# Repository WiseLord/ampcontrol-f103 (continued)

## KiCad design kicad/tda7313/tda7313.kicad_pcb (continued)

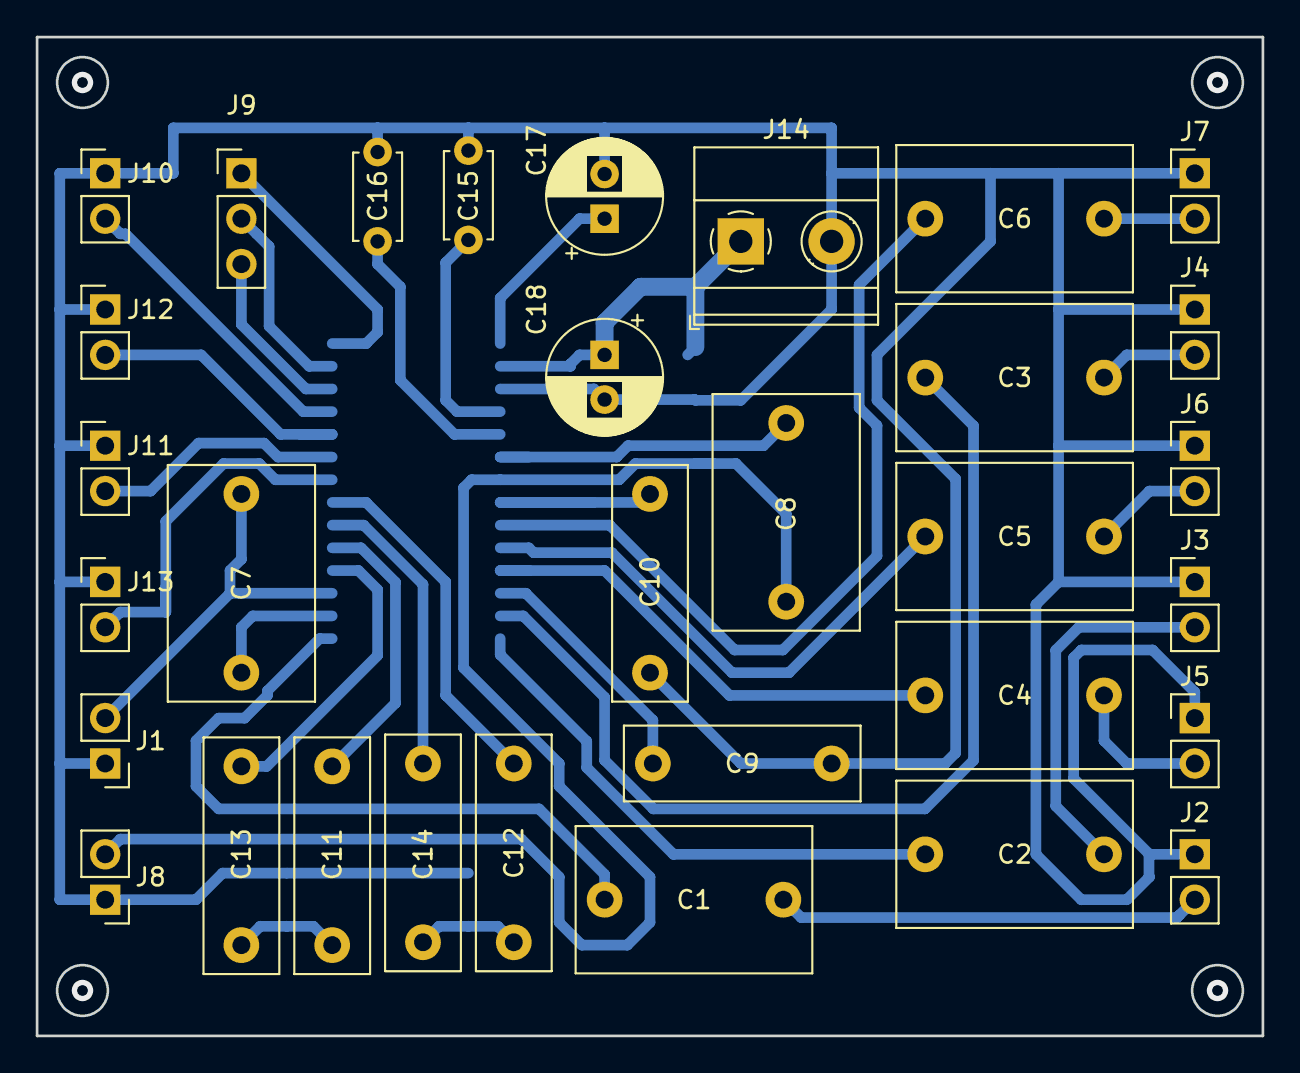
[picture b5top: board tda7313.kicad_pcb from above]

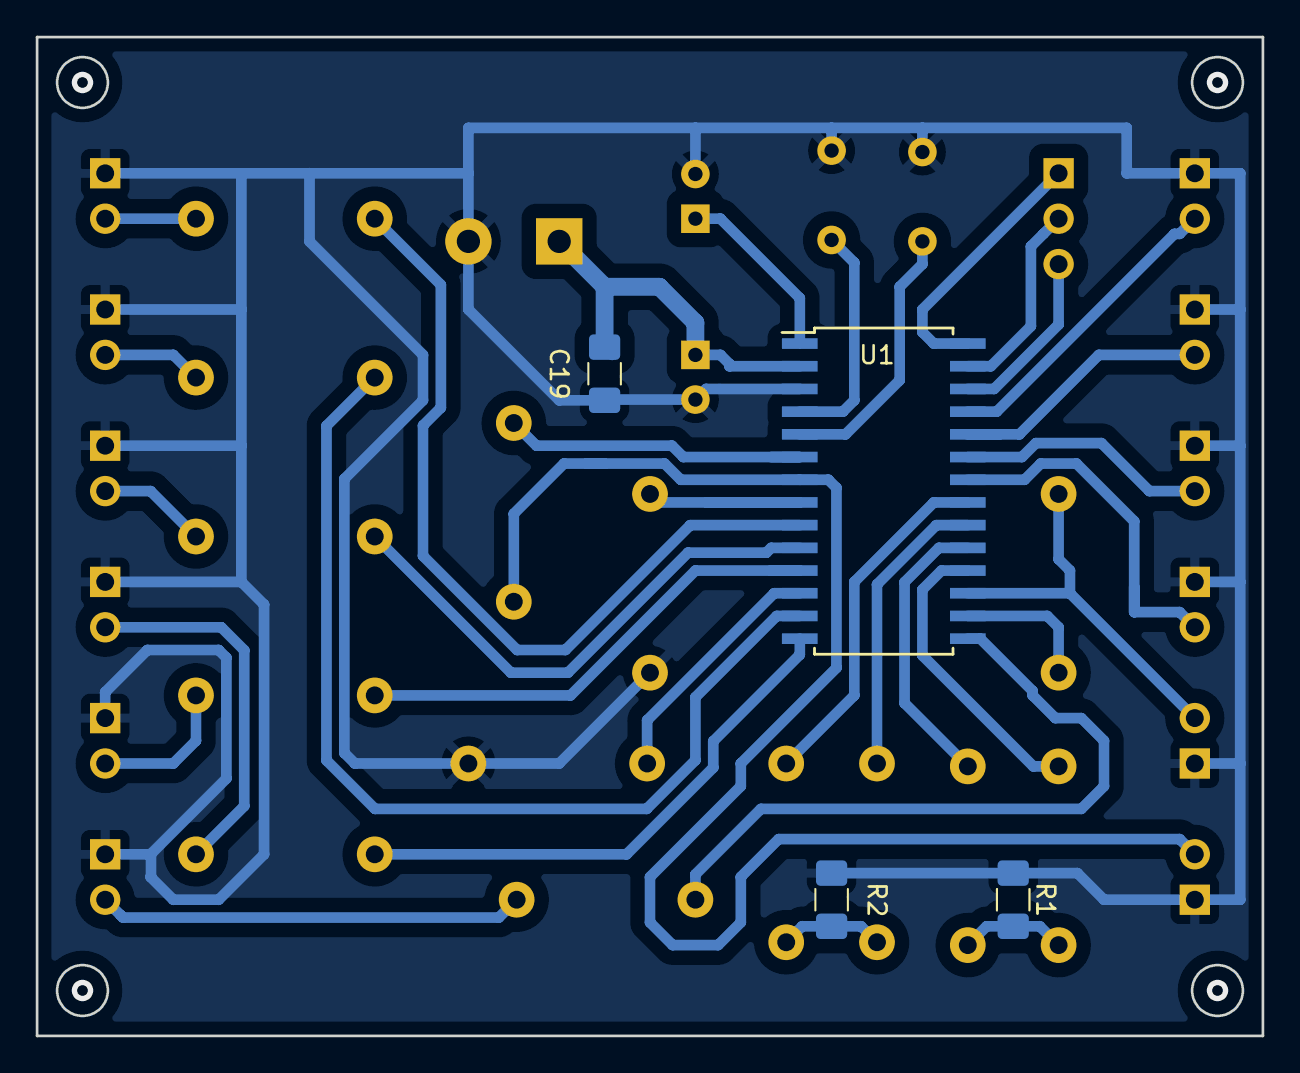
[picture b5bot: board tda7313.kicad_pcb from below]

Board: 2 copper layers, 68.6 x 55.9 mm, 36 parts (4 on the bottom side), 36 nets.

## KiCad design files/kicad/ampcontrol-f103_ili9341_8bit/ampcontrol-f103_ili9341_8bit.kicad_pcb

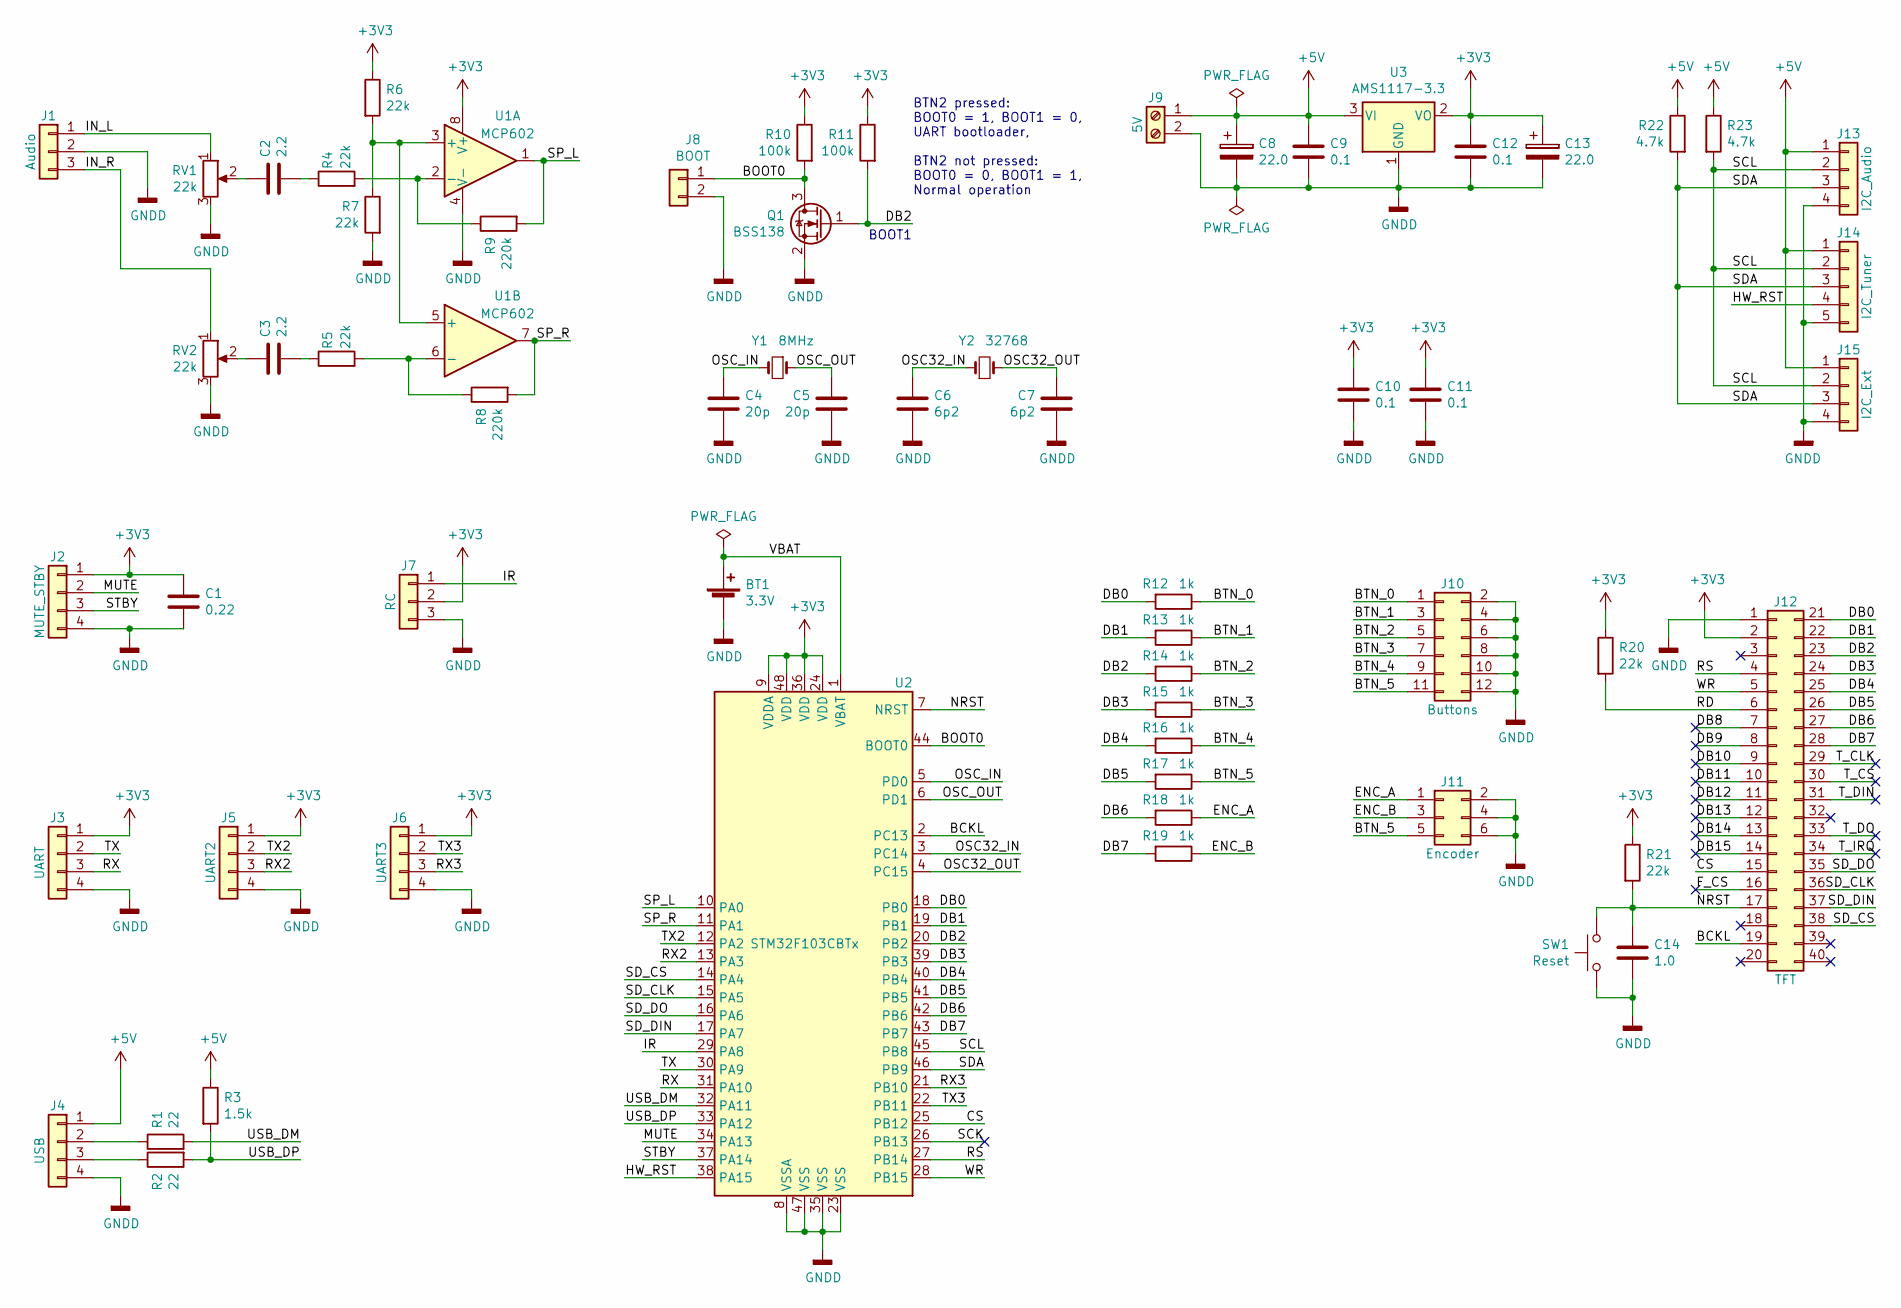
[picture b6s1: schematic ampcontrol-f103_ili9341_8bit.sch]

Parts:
BT1: 3.3V; BatteryHolder_Keystone_103_1x20mm
C1: 0.22; C_1206_3216Metric
C2, C3: 2.2; C_1206_3216Metric
C4, C5: 20p; C_1206_3216Metric
C6, C7: 6p2; C_1206_3216Metric
C8, C13: 22.0; CP_EIA-6032-28_Kemet-C
C9, C10, C11, C12: 0.1; C_1206_3216Metric
C14: 1.0; C_1206_3216Metric
J1: Audio; PinHeader_1x03_P2.54mm_Vertical
J2: MUTE_STBY; PinHeader_1x04_P2.54mm_Vertical
J3: UART; PinHeader_1x04_P2.54mm_Vertical
J4: USB; PinHeader_1x04_P2.54mm_Vertical
J5: UART2; PinHeader_1x04_P2.54mm_Vertical
J6: UART3; PinHeader_1x04_P2.54mm_Vertical
J7: RC; PinHeader_1x03_P2.54mm_Vertical
J8: BOOT; PinHeader_1x02_P2.54mm_Vertical
J9: 5V; TerminalBlock_bornier-2_P5.08mm
J10: Buttons; PinHeader_2x06_P2.54mm_Vertical
J11: Encoder; PinHeader_2x03_P2.54mm_Vertical
J12: TFT; PinSocket_2x20_P2.54mm_Vertical_Top_Bottom
J13: I2C_Audio; PinHeader_1x04_P2.54mm_Vertical
J14: I2C_Tuner; PinHeader_1x05_P2.54mm_Vertical
J15: I2C_Ext; PinHeader_1x04_P2.54mm_Vertical
Q1: BSS138; SOT-23
R1, R2: 22; R_1206_3216Metric
R3: 1.5k; R_1206_3216Metric
R4, R5, R6, R7, R20, R21: 22k; R_1206_3216Metric
R8, R9: 220k; R_1206_3216Metric
R10, R11: 100k; R_1206_3216Metric
R12, R13, R14, R15, R16, R17, R18, R19: 1k; R_1206_3216Metric
R22, R23: 4.7k; R_1206_3216Metric
RV1, RV2: 22k; Potentiometer_Piher_PT-6-V_Vertical
SW1: Reset; SW_PUSH_6mm
U1: MCP602; SOIC-8_3.9x4.9mm_P1.27mm
U2: STM32F103CBTx; LQFP-48_7x7mm_P0.5mm
U3: AMS1117-3.3; SOT-223-3_TabPin2
Y1: 8MHz; Crystal_HC49-4H_Vertical
Y2: 32768; Crystal_C38-LF_D3.0mm_L8.0mm_Vertical

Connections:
+3V3: C1.1, C10.2, C11.2, C12.2, C13.1, J2.1, J3.1, J5.1, J6.1, J7.2, J12.2, R6.1, R10.1, R11.1, R20.1, R21.1, U1.8 (V+), U2.9 (VDDA), U2.24 (VDD), U2.36 (VDD), U2.48 (VDD), U3.2 (VO)
+5V: C8.1, C9.2, J4.1, J9.1, J13.1, J14.1, J15.1, R3.1, R22.1, R23.1, U3.3 (VI)
/BCKL: J12.19, U2.2 (PC13)
/BOOT0: J8.1, Q1.3 (D), R10.2, U2.44 (BOOT0)
/BTN_0: J10.1, R12.1
/BTN_1: J10.3, R13.1
/BTN_2: J10.5, R14.1
/BTN_3: J10.7, R15.1
/BTN_4: J10.9, R16.1
/BTN_5: J10.11, J11.5, R17.1
/CS: J12.15, U2.25 (PB12)
/DB0: J12.21, R12.2, U2.18 (PB0)
/DB1: J12.22, R13.2, U2.19 (PB1)
/DB2: J12.23, Q1.1 (G), R11.2, R14.2, U2.20 (PB2)
/DB3: J12.24, R15.2, U2.39 (PB3)
/DB4: J12.25, R16.2, U2.40 (PB4)
/DB5: J12.26, R17.2, U2.41 (PB5)
/DB6: J12.27, R18.2, U2.42 (PB6)
/DB7: J12.28, R19.2, U2.43 (PB7)
/DB8: J12.7
/DB9: J12.8
/DB10: J12.9
/DB11: J12.10
/DB12: J12.11
/DB13: J12.12
/DB14: J12.13
/DB15: J12.14
/ENC_A: J11.1, R18.1
/ENC_B: J11.3, R19.1
/F_CS: J12.16
/HW_RST: J14.4, U2.38 (PA15)
/IN_L: J1.1, RV1.1
/IN_R: J1.3, RV2.1
/IR: J7.1, U2.29 (PA8)
/MUTE: J2.2, U2.34 (PA13)
/NRST: C14.2, J12.17, R21.2, SW1.1, U2.7 (NRST)
/OSC32_IN: C6.1, U2.3 (PC14), Y2.1
/OSC32_OUT: C7.2, U2.4 (PC15), Y2.2
/OSC_IN: C4.1, U2.5 (PD0), Y1.2
/OSC_OUT: C5.2, U2.6 (PD1), Y1.1
/RD: J12.6, R20.2
/RS: J12.4, U2.27 (PB14)
/RX: J3.3, U2.31 (PA10)
/RX2: J5.3, U2.13 (PA3)
/RX3: J6.3, U2.21 (PB10)
/SCK: U2.26 (PB13)
/SCL: J13.2, J14.2, J15.2, R23.2, U2.45 (PB8)
/SDA: J13.3, J14.3, J15.3, R22.2, U2.46 (PB9)
/SD_CLK: J12.36, U2.15 (PA5)
/SD_CS: J12.38, U2.14 (PA4)
/SD_DIN: J12.37, U2.17 (PA7)
/SD_DO: J12.35, U2.16 (PA6)
/SP_L: R9.2, U1.1, U2.10 (PA0)
/SP_R: R8.2, U1.7, U2.11 (PA1)
/STBY: J2.3, U2.37 (PA14)
/TX: J3.2, U2.30 (PA9)
/TX2: J5.2, U2.12 (PA2)
/TX3: J6.2, U2.22 (PB11)
/T_CLK: J12.29
/T_CS: J12.30
/T_DIN: J12.31
/T_DO: J12.33
/T_IRQ: J12.34
/USB_DM: R1.2, U2.32 (PA11)
/USB_DP: R2.2, R3.2, U2.33 (PA12)
/VBAT: BT1.1 (+), U2.1 (VBAT)
/WR: J12.5, U2.28 (PB15)
GNDD: BT1.2 (-), C1.2, C4.2, C5.1, C6.2, C7.1, C8.2, C9.1, C10.1, C11.1, C12.1, C13.2, C14.1, J1.2, J2.4, J3.4, J4.4, J5.4, J6.4, J7.3, J8.2, J9.2, J10.2, J10.4, J10.6, J10.8, J10.10, J10.12, J11.2, J11.4, J11.6, J12.1, J13.4, J14.5, J15.4, Q1.2 (S), R7.2, RV1.3, RV2.3, SW1.2, U1.4 (V-), U2.8 (VSSA), U2.23 (VSS), U2.35 (VSS), U2.47 (VSS), U3.1 (GND)
unnamed: C2.1, R4.1
unnamed: C2.2, RV1.2
unnamed: C3.1, R5.1
unnamed: C3.2, RV2.2
unnamed: J4.2, R1.1
unnamed: J4.3, R2.1
unnamed: R4.2, R9.1, U1.2 (-)
unnamed: R5.2, R8.1, U1.6 (-)
unnamed: R6.2, R7.1, U1.3 (+), U1.5 (+)

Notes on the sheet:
BOOT1
BTN2 pressed: BOOT0 = 1, BOOT1 = 0, UART bootloader, BTN2 not pressed: BOOT0 = 0, BOOT1 = 1, Normal operation

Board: 2 copper layers, 62 parts (19 on the bottom side), 62 nets, no tracks yet.

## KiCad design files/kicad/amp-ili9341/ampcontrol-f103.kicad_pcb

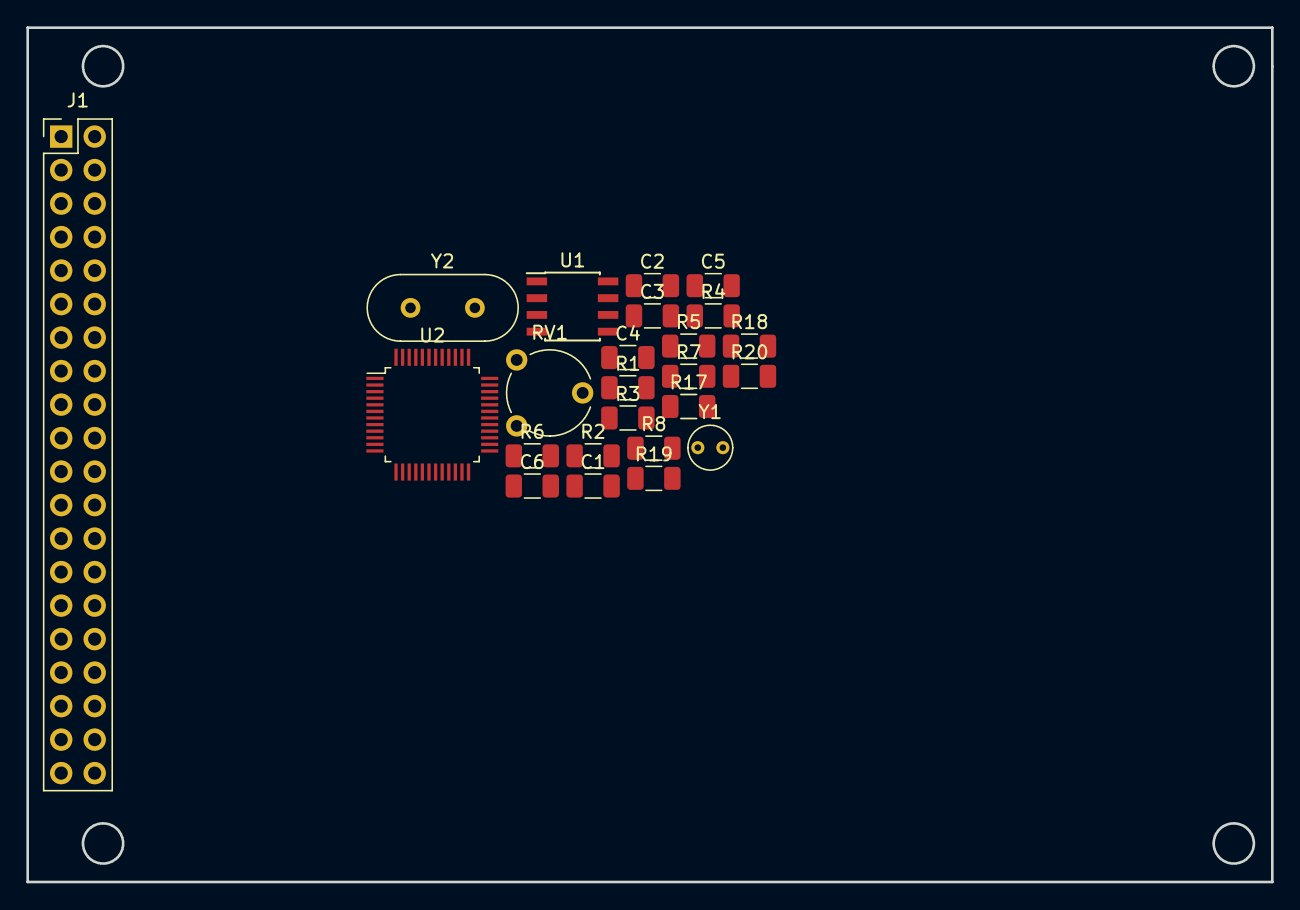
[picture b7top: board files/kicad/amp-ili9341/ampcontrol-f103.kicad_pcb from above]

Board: 2 copper layers, 94.4 x 64.8 mm, 24 parts (0 on the bottom side), 36 nets, no tracks yet.

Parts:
C1, C2, C5, C6: 20p; C_1206_3216Metric
C3, C4: 6p2; C_1206_3216Metric
J1: Conn_LCD; PinSocket_2x20_P2.54mm_Vertical_Top_Bottom
R1, R2: 10k; R_1206_3216Metric
R3, R4, R5, R6, R17, R20: 22k; R_1206_3216Metric
R7, R8: 100k; R_1206_3216Metric
R18, R19: 4k7; R_1206_3216Metric
RV1: 22k; Potentiometer_Piher_PT-6-V_Vertical
U1: MCP602; SOIC-8_3.9x4.9mm_P1.27mm
U2: STM32F103CBTx; LQFP-48_7x7mm_P0.5mm
Y1: 32768; Crystal_C38-LF_D3.0mm_L8.0mm_Vertical
Y2: 8MHz; Crystal_HC49-4H_Vertical

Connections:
+3V3: J1.2, R3.1, R5.1, R17.1, R20.1, U2.24, U2.36, U2.48
+5V: R18.1, R19.1
/BCKL: J1.19, U2.2
/CS: J1.15, U2.43
/DB0: J1.21, U2.10
/DB1: J1.22, U2.11
/DB2: J1.23, U2.12
/DB3: J1.24, U2.13
/DB4: J1.25, U2.14
/DB5: J1.26, U2.15
/DB6: J1.27, U2.16
/DB7: J1.28, U2.17
/NRST: J1.17, R17.2, U2.7
/RD: J1.6, R20.2, U2.40
/RS: J1.4, U2.42
/SCL: R18.2, U2.21
/SDA: R19.2, U2.22
/SD_CLK: J1.36, U2.26
/SD_CS: J1.38, U2.25
/SD_DIN: J1.37, U2.28
/SD_DO: J1.35, U2.27
/SP_L: R7.2, U1.1, U2.18
/SP_R: R8.2, U1.7, U2.19
/WR: J1.5, U2.41
GNDD: C3.2, C4.1, C5.1, C6.1, J1.1, R4.2, R6.2, RV1.3, U2.23, U2.35, U2.47
unnamed: C1.1, R1.1
unnamed: C1.2, RV1.2
unnamed: C2.1, R2.1
unnamed: C3.1, U2.4, Y1.1
unnamed: C4.2, U2.3, Y1.2
unnamed: C5.2, U2.6, Y2.2
unnamed: C6.2, U2.5, Y2.1
unnamed: R1.2, R7.1, U1.2
unnamed: R2.2, R8.1, U1.6
unnamed: R3.2, R4.1, U1.3
unnamed: R5.2, R6.1, U1.5

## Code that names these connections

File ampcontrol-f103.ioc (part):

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Mcu.Name=STM32F103C(8-B)Tx
Mcu.Package=LQFP48
Mcu.UserName=STM32F103C8Tx
PA0-WKUP.GPIOParameters=GPIO_Label
PA0-WKUP.GPIO_Label=LEFT
PA0-WKUP.Signal=ADCx_IN0
PA1.GPIOParameters=GPIO_Label
PA1.GPIO_Label=RIGHT
PA1.Signal=ADCx_IN1
PA10.GPIOParameters=GPIO_Label
PA10.GPIO_Label=RX
PA10.Mode=Asynchronous
PA10.Signal=USART1_RX
PA11.Mode=Device
PA11.Signal=USB_DM
PA12.Mode=Device
PA12.Signal=USB_DP
PA13.GPIOParameters=GPIO_Label
PA13.GPIO_Label=MUTE/SWDIO
PA13.Mode=Serial_Wire
PA13.Signal=SYS_JTMS-SWDIO
PA14.GPIOParameters=GPIO_Label
PA14.GPIO_Label=STBY/SWCLK
PA14.Mode=Serial_Wire
PA14.Signal=SYS_JTCK-SWCLK
PA15.GPIOParameters=GPIO_Label
PA15.GPIO_Label=HW_RST
PA15.Signal=GPIO_Output
PA2.GPIOParameters=GPIO_Label
PA2.GPIO_Label=TX2
PA2.Mode=Asynchronous
PA2.Signal=USART2_TX
PA3.GPIOParameters=GPIO_Label
PA3.GPIO_Label=RX2
PA3.Mode=Asynchronous
PA3.Signal=USART2_RX
PA4.GPIOParameters=GPIO_Label
PA4.GPIO_Label=SD_NSS
PA4.Mode=NSS_Signal_Hard_Input
PA4.Signal=SPI1_NSS
PA5.GPIOParameters=GPIO_Label
PA5.GPIO_Label=SD_SCK
PA5.Mode=Full_Duplex_Master
PA5.Signal=SPI1_SCK
PA6.GPIOParameters=GPIO_Label
PA6.GPIO_Label=SD_MISO
PA6.Mode=Full_Duplex_Master
PA6.Signal=SPI1_MISO
PA7.GPIOParameters=GPIO_Label
PA7.GPIO_Label=SD_MOSI
PA7.Mode=Full_Duplex_Master
PA7.Signal=SPI1_MOSI
PA8.GPIOParameters=GPIO_Label
PA8.GPIO_Label=IR
PA8.Signal=GPXTI8
PA9.GPIOParameters=GPIO_Label
PA9.GPIO_Label=TX
PA9.Mode=Asynchronous
PA9.Signal=USART1_TX
PB0.GPIOParameters=GPIO_Label
PB0.GPIO_Label=BTN_0
PB0.Signal=GPIO_Input
PB1.GPIOParameters=GPIO_Label
PB1.GPIO_Label=BTN_1
PB1.Signal=GPIO_Input
PB10.GPIOParameters=GPIO_Label
PB10.GPIO_Label=TX3
PB10.Mode=Asynchronous
PB10.Signal=USART3_TX
PB11.GPIOParameters=GPIO_Label
PB11.GPIO_Label=RX3
PB11.Mode=Asynchronous
PB11.Signal=USART3_RX
PB12.GPIOParameters=GPIO_Label
PB12.GPIO_Label=DISP_CS
PB12.Mode=NSS_Signal_Hard_Input
PB12.Signal=SPI2_NSS
PB13.GPIOParameters=GPIO_Label
PB13.GPIO_Label=DISP_SCK
PB13.Mode=Full_Duplex_Master
PB13.Signal=SPI2_SCK
PB14.GPIOParameters=GPIO_Label
PB14.GPIO_Label=DISP_DC
PB14.Mode=Full_Duplex_Master
PB14.Signal=SPI2_MISO
PB15.GPIOParameters=GPIO_Label
PB15.GPIO_Label=DISP_SDI
PB15.Mode=Full_Duplex_Master
PB15.Signal=SPI2_MOSI
PB2.GPIOParameters=GPIO_Label
PB2.GPIO_Label=BTN_2
PB2.Signal=GPIO_Input
PB3.GPIOParameters=GPIO_Label
PB3.GPIO_Label=BTN_3
PB3.Signal=GPIO_Input
PB4.GPIOParameters=GPIO_Label
PB4.GPIO_Label=BTN_4
PB4.Signal=GPIO_Input
PB5.GPIOParameters=GPIO_Label
PB5.GPIO_Label=BTN_5
PB5.Signal=GPIO_Input
PB6.GPIOParameters=GPIO_Label
PB6.GPIO_Label=ENC_A
PB6.Signal=GPIO_Input
PB7.GPIOParameters=GPIO_Label
PB7.GPIO_Label=ENC_B
PB7.Signal=GPIO_Input
PB8.GPIOParameters=GPIO_Label
PB8.GPIO_Label=SCL
PB8.Mode=I2C
PB8.Signal=I2C1_SCL
PB9.GPIOParameters=GPIO_Label
PB9.GPIO_Label=SDA
PB9.Mode=I2C
PB9.Signal=I2C1_SDA
PC13-TAMPER-RTC.GPIOParameters=GPIO_Label
PC13-TAMPER-RTC.GPIO_Label=DISP_BL
PC13-TAMPER-RTC.Signal=GPIO_Output
PC14-OSC32_IN.Mode=LSE-External-Oscillator
PC14-OSC32_IN.Signal=RCC_OSC32_IN
PC15-OSC32_OUT.Mode=LSE-External-Oscillator
PC15-OSC32_OUT.Signal=RCC_OSC32_OUT
PD0-OSC_IN.Mode=HSE-External-Oscillator
PD0-OSC_IN.Signal=RCC_OSC_IN
PD1-OSC_OUT.Mode=HSE-External-Oscillator
PD1-OSC_OUT.Signal=RCC_OSC_OUT
RCC.SYSCLKFreq_VALUE=72000000
RCC.SYSCLKSource=RCC_SYSCLKSOURCE_PLLCLK
board=ampcontrol-f103

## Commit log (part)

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2019-11-12 Fix I2C compile error on F303
2019-11-12 Fix brightness control in display emulator
2019-11-14 Rework buttons handling
2019-12-12 KiCad: Add symbol for TDA7719
2019-12-13 PCB for TDA7719
2019-12-14 Fix TDA731x mute
2019-12-14 Initial TDA7719 support
2019-12-14 Support loudness and gain control on TDA7719
2019-12-15 Sync display driver with wl_lcd-f103
2019-12-17 Use memory functions from stdlib
2019-12-18 Fix display emulator build
2019-12-26 Fix crash on drawing NULL string
2019-12-26 Fix memory leaks
2019-12-27 Modify pin description
2019-12-27 Schematic: map MUTE/STBY to PB11/PB10, that are de-facto have been used
2019-12-27 Fix MUTE/STBY on PB11/PB10
2019-12-27 Fix display emulator build error
2020-01-03 Support vertical gradient drawing
2020-01-06 Spectrum gradients support
2020-01-11 Optimize Makefile for easier STM32 MCU selection
2020-01-11 Fix eemul for F303CB
2020-01-11 Refactor eeprom emulator module
2020-01-11 Fix ldscripts
2020-01-12 Rework action queue
2020-01-12 Separate I2C IO expander module
2020-01-12 Remove .visible flag from action
2020-01-12 Remove 'clear' flag from screenShow
2020-01-12 Refactored screen mode
2020-01-14 Rework icon hints
2020-01-14 Remove DEBUG_FPS macro
2020-01-15 Move Hann window function to fft
2020-01-16 Stop on standby timer timeout
2020-01-16 Rework build not to use vpath
2020-01-16 Add OBJ_DIR var to Makefile
2020-01-19 MUTE/STBY pins refactoring
2020-01-19 Simplify handling NVIC priorities
2020-01-19 Refactored settingsGet/menuGetValue
2020-01-19 Move spectrum timer init to amp init
2020-01-19 Sw timers refactoring
2020-01-19 Refactor I2C reinit on input powering
2020-01-28 Fix tone control on TDA7418
2020-01-28 Small clock-related fixes
2020-02-01 Possibility to enable/disable USB support
2020-02-01 Refactored colors
2020-02-02 Don't use floating input mode
2020-02-02 Remove utils
2020-02-04 Small changes in schematic/PCB
2020-02-04 Fix reading display brightness on init
2020-02-04 Soft unmute
2020-02-06 Amp control improvements
2020-02-06 Move the sources to the subidir
2020-02-07 Use STEP_MULT
2020-02-07 Refactor audio/tuner settings handling
2020-02-10 Don't work with PCF8574 if disabled
2020-02-11 I2C refactoring
2020-02-11 Decrease I2C buffer
2020-02-11 Fix I2C1 clock source
2020-02-11 Update I2C library - slave callbacks implemented
2020-02-15 Update I2C library
2020-02-16 Basic BT201 support - play/next/prev
2020-02-16 Fix report all
2020-02-16 Show media icon hint on BT screen also
2020-02-25 Update config to use recent openocd on f103
2020-02-25 Simplify openocd configs
2020-02-25 Fix flash definitions for STM32F3
2020-03-02 Fix sending mediakey to PC when tuner input is active
2020-03-02 Simplify tuner station/grid mode selection
2020-03-02 Fix station mode
2020-03-02 Proper handling AUDIO_IC_NO
2020-03-02 Fix audio menu after power lost
2020-03-02 Use less RAM for I2C
2020-03-06 Update UA translation
    Thanks to Nadim
2020-03-06 Fixes for UA translation
    Thanks to Duke
2020-03-06 Finalize BY/RU/TR/UA translations
2020-03-06 Enable LTO for .c files
2020-03-06 Don't reboot KaRadio on input change
2020-03-06 Add the file with KaRadio URLs
2020-03-07 Support direct input set via control module
2020-03-08 Support volume/bass/middle/treble inc/dec from uart control
2020-03-08 Add help on UART control
2020-03-12 Sync with h-ms1110
2020-03-14 Add audio param set, audio IC request
2020-03-14 Add some tuner controls
2020-03-14 Small simplify in rc lib
2020-03-14 Check for audio signal presence by hardware
2020-03-14 Rework getting spectrum
2020-03-14 Remove sp.ready flag
2020-03-14 Remove sp.redraw flag
2020-03-14 Move spData to canvas side
2020-03-15 Modify glcd initialization
2020-03-16 Support BT input parsing
2020-03-16 Simplify lineparse
2020-03-17 Support input selection on BT201
2020-03-17 Support BT next input on gpio-based modules
2020-03-17 Fix build for F303
2020-03-18 Fix and simplify waterfall drawing
2020-03-18 Fix signal detection
2020-03-19 Support of song names on BT201
2020-03-19 Fix media keys drawing on BT screen
2020-03-20 Permanently enable debug
2020-03-20 Optimize BT201 parsing
2020-03-21 Refactored KaRadio parsing, code cleanup
2020-03-21 Remove extension from song name from BT201
2020-03-21 Change some defaults for my needs :)
2020-03-21 Add more symbols to some fonts
2020-03-21 Modify fonts
2020-03-21 Update icons
2020-03-21 Small code alignments
2020-03-22 Common spectrum behaviour on all screens
2020-03-22 Modify some icons
2020-03-24 Fix for F303 build
2020-03-24 Update UA translation
2020-03-27 Icon hints on Karadio also
2020-03-28 Add option to show audio values in dB
2020-03-29 More correct textEdit drawing
2020-03-29 Support entering KaRadio station by digit buttons
2020-03-30 Fix compilation warning
2020-04-18 Test HX8357 support
2020-04-19 Added readme.md
2020-04-26 Refactor palette and widgets
2020-04-30 Rework volume restoring
2020-04-30 Fix terminus-12 font
2020-05-03 Show RC code in hex
2020-05-07 Sync with h-ms1110 project
2020-05-08 Fix bool param displaying
2020-05-09 Move intype out of audio
2020-05-30 Separate active low settings for MUTE and STBY
2020-05-30 Rework SWD handling
2020-05-30 Sync display code with h-ms1110
2020-06-02 Sync spectrum code with h-ms1110 project
2020-06-02 Fix input on SPI displays
2020-06-14 Add FAN control circuit
2020-07-09 Refactor display rotate to be boolean
2020-07-09 Portrate orientation support
2020-07-09 Combine rotate and portrate to common orientation enum
2020-07-11 Sync display code with wl-lcd
2020-08-06 Sync display code, refactoring backlight functions
2020-09-05 Define input port
2020-09-05 Remove hwlibs.h dep
2020-09-05 SSD1283A rotation support
2020-09-05 Distinguish hw-related display code
2020-09-06 Fix SSD1322 build
2020-09-06 Isolate dispdrv
2020-09-06 Get rid of STM32 LL library in display driver
2020-09-08 Optimize strings drawing
2020-09-25 Sync avr display defines
2020-11-03 Fix mounting holes on PCB for 2.8 display
2020-11-18 Adjust Flash size in linker scripts
2020-11-18 Make PT232x able to work in 2.0, 2.1, 4.0, 4.1 modes
2020-11-18 Add 4.1 audio mode
2020-11-18 Add settings for future audio mode
2020-11-18 Fix TDA7439 volume control
2020-11-18 Rework raw balance
2020-11-18 Make rear speakers able to act as bass ones
2020-11-18 Check for supported audio mode
2020-11-18 Enable LP filter in sub modes for TDA7719
2020-11-19 Play/stop BT when entering/leaving input
2020-11-20 Improve subwoofer gain on TDA7719
2020-11-22 Reduce audio clicks when entering standby
2020-12-11 Change display params EE offsets
2020-12-11 Move settings GET and SET functions to menu.c
2020-12-11 Sync settings, audio and tuner with h-ms1110
2020-12-11 Sync utils with h-ms1110
2020-12-12 Small refactoring RDA580x
2020-12-12 Modify RDS
2020-12-20 Sync tuner code with H-MS1110
2020-12-23 Remove inversion in ST7735
2021-01-20 More correct TDA7719 mute
2021-01-25 Fix PC belarusian label
2021-01-25 Refactored media keys
2021-01-26 Sync display driver with h-ms1110
2021-01-27 Replace karadio control by mpc one
2021-01-28 Replace Mixer with MPC
2021-01-28 Basic support of MPD via mpd-uart.py service
2021-01-29 Fix low FPS on MPC
2021-02-02 Save 256 bytes of RAM
2021-02-02 Share spectrum draw data and stars screensaver one
2021-02-04 Icons for MPD status
2021-02-10 Add swtimers debug feature
2021-02-10 Rework software timers
2021-02-10 Make time setup easier
2021-02-11 Sync spectrum lib with h-ms1110
2021-02-15 Fix hiding silence timer
2021-02-15 Separate amp.c and amp_main.c
2021-02-15 Refactoring code
2021-02-15 Rework standby timers and screensaver
2021-02-15 Improve bluetooth icons
2021-02-16 Fix includes
2021-02-16 Reduce checkSignal sensitivity
2021-02-17 Fix RC setup
2021-02-18 Support forced mono for TEA5767
2021-02-18 Move to the latest STM32 libraries
2021-02-18 Remove adc workaround due to fix in HAL library
2021-02-22 Update MPD-related scripts
2021-02-23 Improve menu output
2021-02-24 Support "Playlist_NNN" enetered by digits in MPD
2021-02-26 Add LCD display connection schematics
2021-02-27 Add/modify some docs
2021-02-27 Fix screensaver on big displays
2021-02-28 Add MPD power switch request
2021-02-28 Add RPI power schematic
2021-02-28 Support MPD poweroff feature
2021-03-01 Split MPC and KaRadio drawing
2021-03-01 Fix MPD icons shadowed by number
2021-03-01 Restyle GLCD library
2021-03-01 Fix rpi-power schematics
2021-03-01 Update time from KaRadio support
2021-03-02 Make stars screensaver smoother
2021-03-02 Update MPD scripts and handling
2021-03-03 Fix fantom encoder events
2021-03-15 Fix MPD IP showing on radio stopped
2021-03-15 Reset menu item by long press BTN_5
2021-03-16 Switch to BT201 on USB or SDCARD insert
2021-03-16 Fix BTN2 bounce
2021-03-20 Fix pausing on MPD
2021-03-20 Fix IP showing on KaRadio
2021-03-25 Combine audio flags into one variable
2021-03-25 Use common audioflag set/reset function
2021-03-27 Less noise-sensitive spectrum
2021-03-27 Sync tuner with h-ms1110 project
2021-03-28 Icons refactoring
2021-03-29 Refactored menu
2021-03-29 Optimize audio tunes
2021-03-29 Fix KaRadio IP
2021-03-30 Fix alarm
2021-03-30 Remove menu reset functionality
2021-03-30 Simplify settings mapping
2021-03-30 Optimize timer drawing
2021-03-31 Remove settings for SP_DEMO
2021-03-31 Rework spGetDb function
2021-04-02 Add extra controls for TDA7418
2021-04-04 Less threshold for signal detection
2021-04-04 Fix rtc correction settings
2021-04-05 Sync MPD code with h-ms1110
2021-06-12 Rework KaRadio docs
2021-06-12 KaRadio: always show IP on stop
2021-06-15 Remove uart control module
2021-06-15 Add RDA5807FP symbol to ampcontrol-f103.lib
2021-06-15 BT: avoid screen clear on track change
2021-06-17 Get rid of sscanf
2021-06-17 Refactor IP and AP parsing on KaRadio
2021-06-17 More parsing for KaRadio32
2021-06-18 Scroll long meta text support.
2021-06-18 Improve char output
2021-06-18 Slower scroll ans spectrum
2021-06-18 Get rid of malloc
2021-06-20 Add info about BT moudles support
2021-07-09 Common waiting for input
2021-09-01 Sync audio code with h-ms1110
2021-09-01 Fix crash on tuning NULL tune
2021-09-01 Fix audioGetInputCount() function
2022-01-08 Add mpd-uart init script
2022-02-14 Refactor tuner (allow to include L7213X)
2022-02-15 Init syscounter used for udelays
2022-02-19 Move block-sch to Kicad 6
2022-02-19 Move fancontrol to Kicad 6
2022-02-19 Move karadio-red to Kicad 6
2022-02-19 Move pwr_33x2 to Kicad 6
2022-02-19 Move rpi_power to Kicad 6
2022-02-19 Move tda7313 to Kicad 6
2022-04-14 Swap MUTE and STBY in documentation
2022-04-14 Swap MUTE and STBY in pin description
2022-04-14 Swap MUTE and STBY in schematic, with no PCB change
2022-06-22 Sync display drivers with wl-lcd project
2023-04-01 Count failed builds
2023-04-01 Setup github actions
2024-03-06 specturm.c: make utils- and settings-independent
2024-03-06 Remove display driver dependency on utils.h
2024-03-06 Add display size to output file name
2024-03-06 Add GPIO debug
2024-03-06 Fix RELAY initialization
2024-03-06 Fix audio glitches on input change / stby exit
2024-03-06 Never use SWD when RELAY is selected.
    RELAY "audioproc" uses these pins to control motorized resistor,
    so in standby mode is should not reinit pins to SWD.
2024-03-06 Switch to Node 20 actions
2024-03-09 Fix typos in filters for TDA7418/TDA7719
2024-04-30 kicad: sch: Mark R25 as not installed
2024-06-01 Update block-sch to Kicad 7
2024-06-01 Update karadio-red to Kicad 7
2024-06-01 Update ampcontrol-f103 to Kicad 7
2024-06-01 Update tda7313 to Kicad 7
2024-06-01 Update tda7919 to Kicad 7
2024-06-01 Update lcd-connection to Kicad 7
2024-06-01 Update p2r_33x2 to Kicad 7
2024-08-05 Build SPI variants for all displays
    New SPI firmwares are not tested, but at least can be tried.
2024-09-01 Init I2C expander on fiwmare start
2024-11-15 Add ILI9488 and 18-bit pixel format support
2025-06-29 Set stereo spectrum by default
2025-06-29 Use global aPar pointer
2025-06-30 inputs
2025-06-30 Fix encRes = 0
2025-06-30 tune=group
2025-06-30 tunes
